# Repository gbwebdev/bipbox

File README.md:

# Bipbox

A self-hosted communication device for children — a wooden box with a thermal
printer, a telegraph key and a walkie-talkie, so that two kids in two different
homes can write, beep and talk to each other.

> **Status: in development.** The hardware exists (two boxes built); the
> software is being written. See [`docs/architecture.md`](docs/architecture.md).

## What it does

| Feature | |
|---|---|
| **Telex** | Family members log into a web page and send a text, a drawing or a photo. It prints on the box's thermal printer within seconds. |
| **Telegraphy** | Press the button on your box and the orange lamp lights up on the other one, with an optional beep. Nothing more — that is the charm. |
| **VoIP** | Squeeze the PTT on the shoulder speakermic and talk; your voice comes out of the other box's speaker. |

Boxes are grouped into **channels**. Everyone in a channel can beep and talk to
each other. People without a box can join from a browser.

## Hardware

Each box contains a Raspberry Pi Zero W, a MeanWell RS15-5 supply, a 4-port USB
hub, a USB sound card, an ESC/POS thermal printer and a homemade HAT that drives
four status lamps through a 74HCT595 and reads the buttons.

KiCad and FreeCAD sources are in [`CAD/`](CAD/) so you can build your own.

## Repository layout

```
server/   FastAPI server + Janus, deployed with docker-compose
device/   bipboxd daemon and the Pi's local management console
image/    pi-gen configuration producing a ready-to-flash SD image
docs/     architecture, specifications, hardware notes
CAD/      KiCad (HAT) and FreeCAD (enclosure)
```

## Documentation

| | |
|---|---|
| [`docs/architecture.md`](docs/architecture.md) | the design: topology, pin map, data model, protocol, security |
| [`docs/voip-options.md`](docs/voip-options.md) | why the voice path is Janus AudioBridge and not Mumble or WebRTC |
| [`docs/open-questions.md`](docs/open-questions.md) | the decisions behind the design, and why |
| [`docs/workflow.md`](docs/workflow.md) | branches, commits, releases |
| [`context.md`](context.md) | the original description of the project |

## Hardware bring-up

Before any of the software exists, the HAT can be tested on its own:

```bash
sudo apt install python3-spidev python3-gpiozero
sudo python3 device/tools/wiring_test.py
```

It discovers the shift-register bit order, measures button bounce, finds a
speaker-safe volume ceiling and prints a test ticket. See
[architecture.md §3.5](docs/architecture.md).

## Licensing

Two licences, scoped by what they cover:

| | |
|---|---|
| **Software** — everything outside `CAD/` | [MIT](LICENSE) |
| **Hardware** — the KiCad and FreeCAD sources in `CAD/` | [CERN-OHL-S v2](CAD/LICENSE) (strongly reciprocal) |

So you may do as you like with the code, and if you build on the board or the
enclosure and distribute the result, those improvements stay open.

## Acknowledgements

Bipbox grows out of [telex](https://github.com/gbwebdev/telex), an earlier
message-to-thermal-printer project; its printer handling, ESC/POS layout and
drawing tool are carried over here.

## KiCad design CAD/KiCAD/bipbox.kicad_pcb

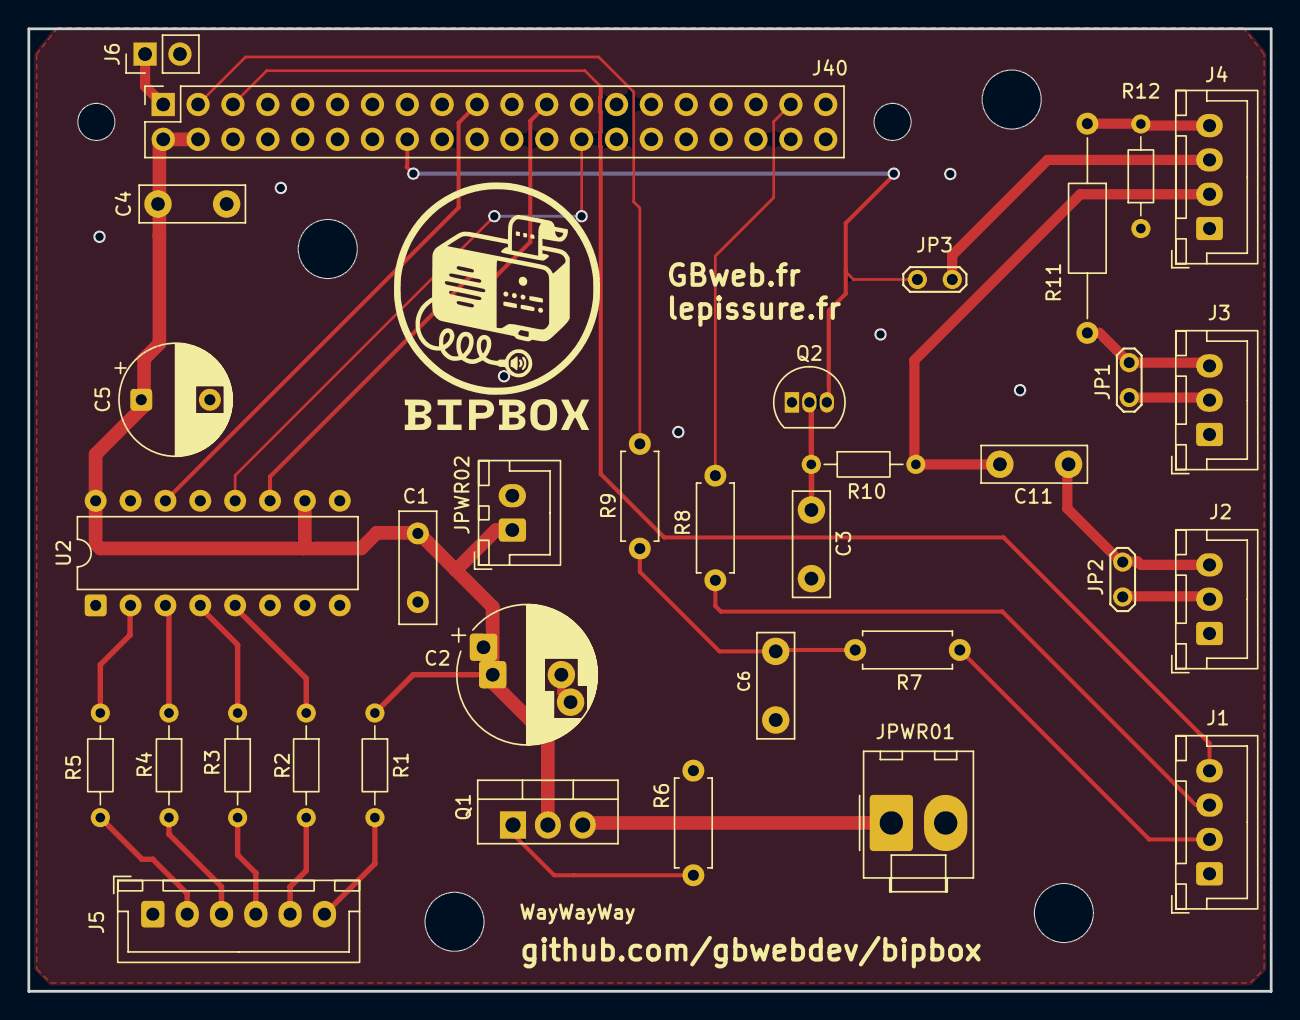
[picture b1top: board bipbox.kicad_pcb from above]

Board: 2 copper layers, 90.5 x 70.1 mm, 36 parts (0 on the bottom side), 32 nets.

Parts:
C1: 100n; C_Disc_D8.0mm_W2.5mm_P5.00mm
C2: 470u; CP_Radial_D10.0mm_P5.00mm_P7.50mm
C3, C4: 100n; C_Disc_D7.5mm_W2.5mm_P5.00mm
C5: 220u; CP_Radial_D8.0mm_P5.00mm
C6: 2.2u; C_Disc_D7.5mm_W2.5mm_P5.00mm
C11: 1u; C_Disc_D7.5mm_W2.5mm_P5.00mm
J1, J4: Conn_01x04_Pin; JST_XH_B4B-XH-A_1x04_P2.50mm_Vertical
J2, J3: Conn_01x03_Pin; JST_XH_B3B-XH-A_1x03_P2.50mm_Vertical
J5: Conn_01x06_Pin; JST_XH_B6B-XH-A_1x06_P2.50mm_Vertical
J6: Conn_01x02_Pin; PinHeader_1x02_P2.54mm_Vertical
J40: GPIO; PinSocket_2x20_P2.54mm_Vertical
JP1, JP2, JP3: Jumper_2_Small_Open; TestPoint_2Pads_Pitch2.54mm_Drill0.8mm
JPWR01: Molex_KK-396_A-41791-0002_1x02_P3.96mm_Vertical
JPWR02: JST_XH_B2B-XH-A_1x02_P2.50mm_Vertical
MH1, MH2: MountingHole_2.7mm_M2.5
Q1: IRF4905; TO-220-3_Vertical
Q2: 2N7000; TO-92_Inline
R1, R2, R5: 180; R_Axial_DIN0204_L3.6mm_D1.6mm_P7.62mm_Horizontal
R3, R4: 300; R_Axial_DIN0204_L3.6mm_D1.6mm_P7.62mm_Horizontal
R6, R9: 10k; R_Axial_DIN0207_L6.3mm_D2.5mm_P7.62mm_Horizontal
R7, R8: 1k; R_Axial_DIN0207_L6.3mm_D2.5mm_P7.62mm_Horizontal
R10: 10k; R_Axial_DIN0204_L3.6mm_D1.6mm_P7.62mm_Horizontal
R11: 22; R_Axial_DIN0207_L6.3mm_D2.5mm_P15.24mm_Horizontal
R12: 47; R_Axial_DIN0204_L3.6mm_D1.6mm_P7.62mm_Horizontal
U2: 74HC595; DIP-16_W7.62mm

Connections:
+3V3: J6.1, J40.1, J40.17
+5VD: C1.2, C2.1, C4.1, C5.1, J40.2, J40.4, JPWR02.1, Q1.2 (D), R1.1, U2.10 (~SRCLR), U2.16 (VCC)
/GPIO2/SDA1: J40.3, R9.1
/GPIO3/SCL1: J1.4, J40.5
/GPIO7/SPI0.CE1: J40.26, U2.12 (RCLK)
/GPIO10/SPI0.MOSI: J40.19, U2.14 (SER)
/GPIO11/SPI0.SCLK: J40.23, U2.11 (SRCLK)
/GPIO23: J40.16, JP3.1 (A), Q2.3 (D)
/GPIO26: J40.37, R8.1
GND: C1.1, C2.2, C3.2, C4.2, C5.2, C6.2, J1.1, J2.1, J3.1, J4.1, J5.1, J6.2, J40.6, J40.9, J40.14, J40.20, J40.25, J40.30, J40.34, J40.39, JPWR01.2, JPWR02.2, Q2.1 (S), R6.2, R12.1, U2.8 (GND), U2.13 (~OE)
unnamed: C6.1, R7.1, R9.2
unnamed: J1.2, R7.2
unnamed: J1.3, R8.2
unnamed: J2.2, JP2.2 (B)
unnamed: C11.2, J2.3, JP2.1 (A)
unnamed: J3.2, JP1.2 (B)
unnamed: J3.3, JP1.1 (A), R11.2
unnamed: C11.1, J4.2, R10.2
unnamed: J4.3, JP3.2 (B)
unnamed: J4.4, R11.1, R12.2
unnamed: J5.2, R5.2
unnamed: J5.3, R4.2
unnamed: J5.4, R3.2
unnamed: J5.5, R2.2
unnamed: J5.6, R1.2
unnamed: JPWR01.1, Q1.3 (S)
unnamed: Q1.1 (G), R6.1
unnamed: C3.1, Q2.2 (G), R10.1
unnamed: R5.1, U2.2 (QC)
unnamed: R4.1, U2.3 (QD)
unnamed: R3.1, U2.4 (QE)
unnamed: R2.1, U2.5 (QF)
